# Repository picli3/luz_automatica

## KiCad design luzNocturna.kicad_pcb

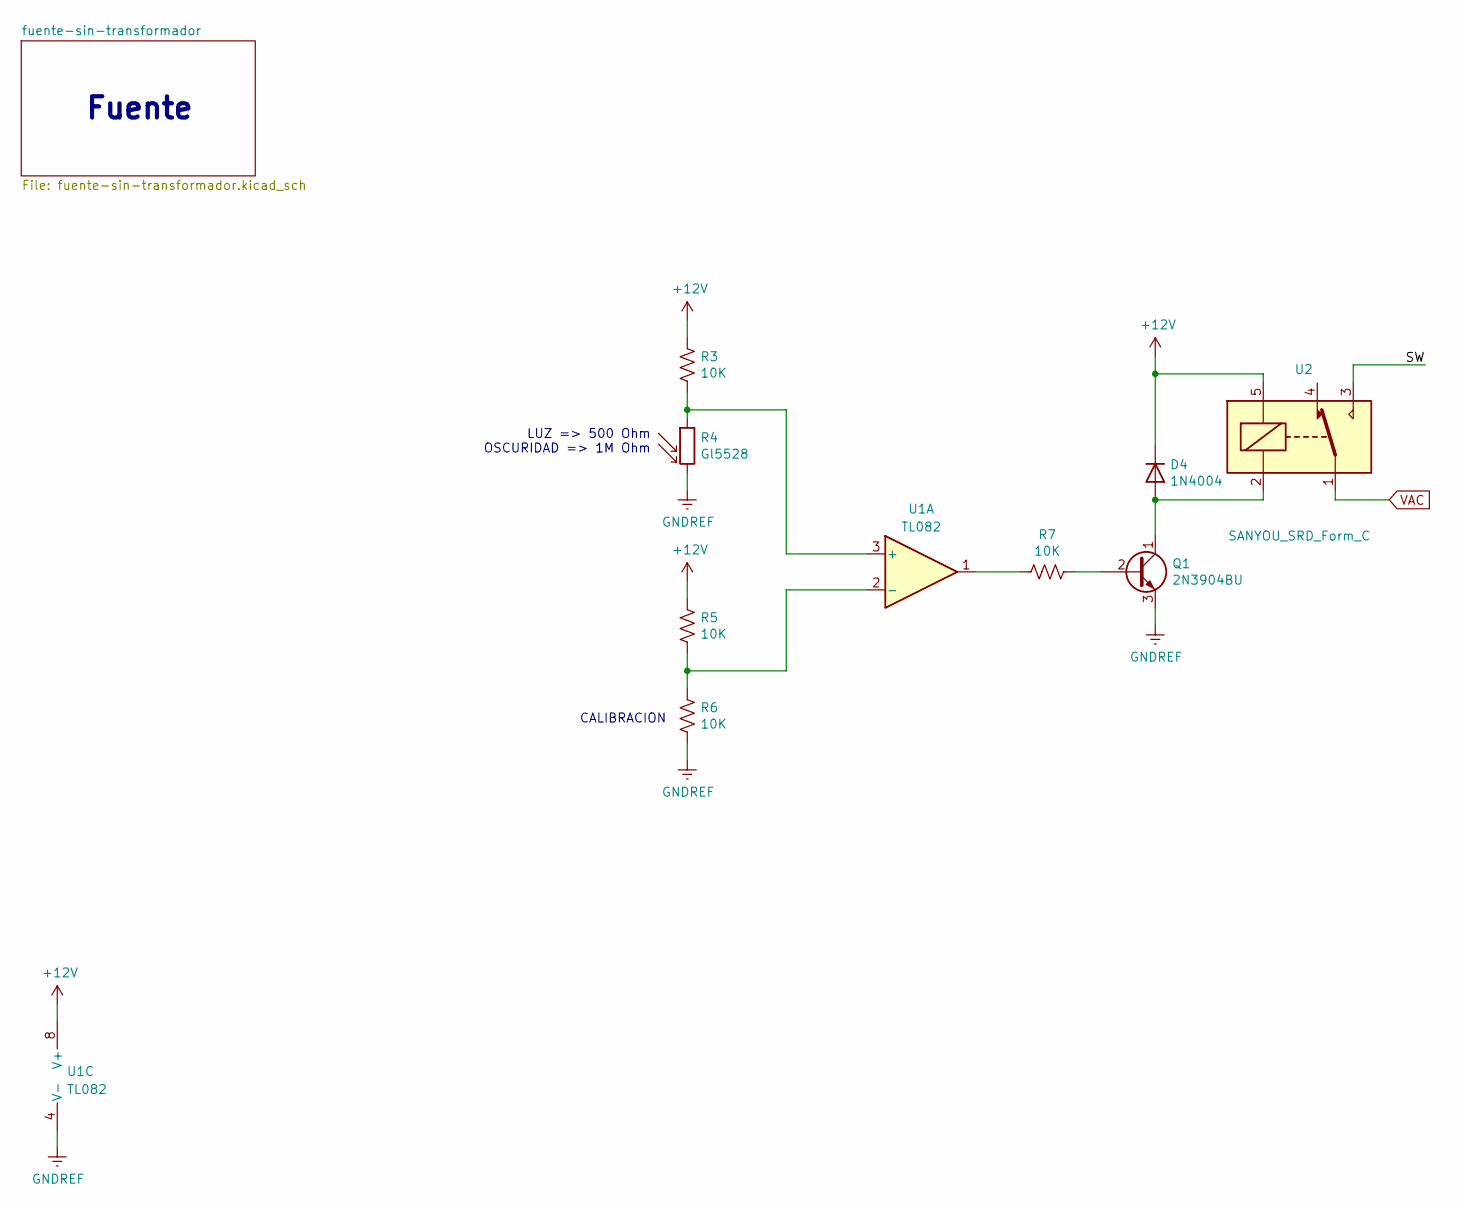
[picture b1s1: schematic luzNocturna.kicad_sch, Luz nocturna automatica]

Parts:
D4: 1N4004; D_DO-41_SOD81_P10.16mm_Horizontal; Mfg Part # 1N4004-T
Q1: 2N3904BU; TO-92; Mfg Part # 2N3904BU
R3, R5, R6, R7: 10K; R_Axial_DIN0411_L9.9mm_D3.6mm_P12.70mm_Horizontal
R4: Gl5528; R_Axial_DIN0516_L15.5mm_D5.0mm_P5.08mm_Vertical; Mfg Part # Gl5528
U1: TL082; DIP-8_W7.62mm; Mfg Part # TL082IP
U2: SANYOU_SRD_Form_C; Relay_SPDT_SANYOU_SRD_Series_Form_C; Mfg Part # ORWH-SH-124D1F,000

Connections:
+12V: D4.1 (K), R3.2, R5.2, U1.8 (V+), U2.5; also elsewhere on the board
/SW: U2.3
GNDREF: Q1.3 (E), R4.2, R6.1, U1.4 (V-); also elsewhere on the board
unnamed: D4.2 (A), Q1.1 (C), U2.2
unnamed: Q1.2 (B), R7.1
unnamed: R7.2, U1.1
unnamed: R3.1, R4.1, U1.3 (+)
unnamed: R5.1, R6.2, U1.2 (-)
VAC: U2.1; also elsewhere on the board

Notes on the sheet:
LUZ => 500 Ohm OSCURIDAD => 1M Ohm
Fuente
CALIBRACION

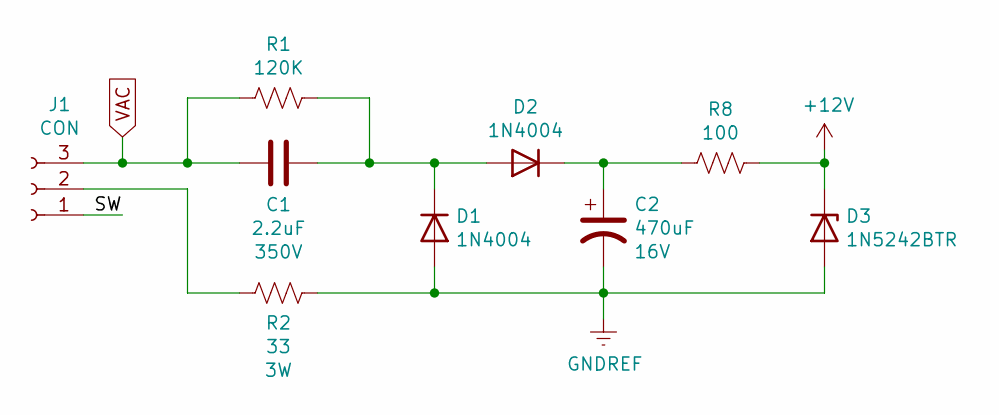
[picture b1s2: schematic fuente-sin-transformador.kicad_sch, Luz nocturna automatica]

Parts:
C1: 2.2uF; C_Rect_L29.0mm_W11.0mm_P27.50mm_MKT; Mfg Part # ECQ-E4225KF
C2: 470uF; CP_Radial_D8.0mm_P3.50mm; Mfg Part # 16ZLH470MEFC8X11.5
D1, D2: 1N4004; D_DO-41_SOD81_P10.16mm_Horizontal; Mfg Part # 1N4004-T
D3: 1N5242BTR; D_DO-35_SOD27_P7.62mm_Horizontal; Mfg Part # 1N5242BTR
J1: CON; TerminalBlock_bornier-3_P5.08mm; Mfg Part # DNP
R1: 120K; R_Axial_DIN0411_L9.9mm_D3.6mm_P12.70mm_Horizontal
R2: 33; R_Axial_DIN0414_L11.9mm_D4.5mm_P15.24mm_Horizontal; Mfg Part # PNP300JR-73-33R
R8: 100; R_Axial_DIN0411_L9.9mm_D3.6mm_P12.70mm_Horizontal

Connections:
+12V: D3.1 (K), R8.1; also elsewhere on the board
/fuente-sin-transformador/SW: J1.1
GNDREF: C2.2, D1.2 (A), D3.2 (A), R2.1; also elsewhere on the board
unnamed: C1.1, D1.1 (K), D2.2 (A), R1.1
unnamed: C2.1, D2.1 (K), R8.2
unnamed: J1.2, R2.2
VAC: C1.2, J1.3, R1.2; also elsewhere on the board

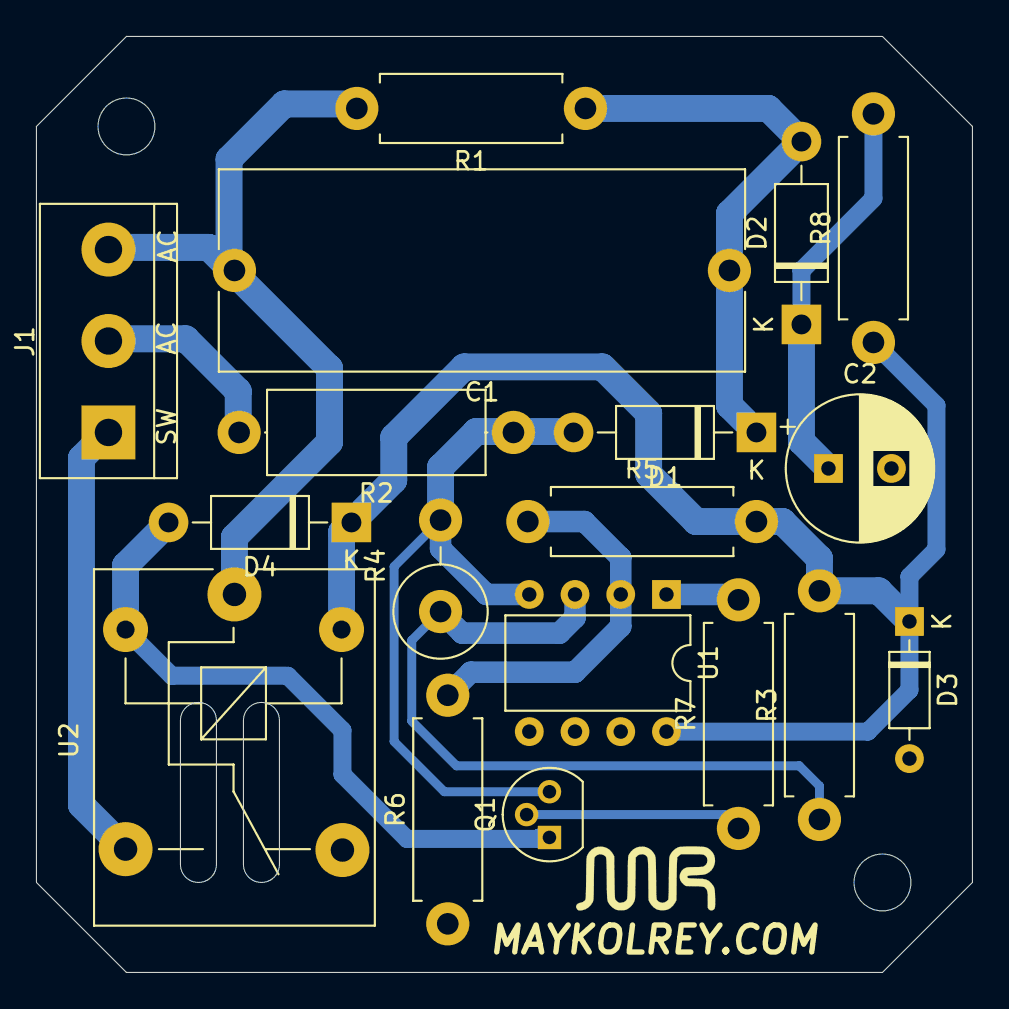
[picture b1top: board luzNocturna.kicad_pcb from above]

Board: 2 copper layers, 52.0 x 52.0 mm, 18 parts (0 on the bottom side), 11 nets.

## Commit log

2020-09-06 listo para fabricar
2020-09-06 agregando pdf
2020-09-06 agregando logo
2023-03-17 actualizando a version 7, aun no se pueden ver los modelos 3D
